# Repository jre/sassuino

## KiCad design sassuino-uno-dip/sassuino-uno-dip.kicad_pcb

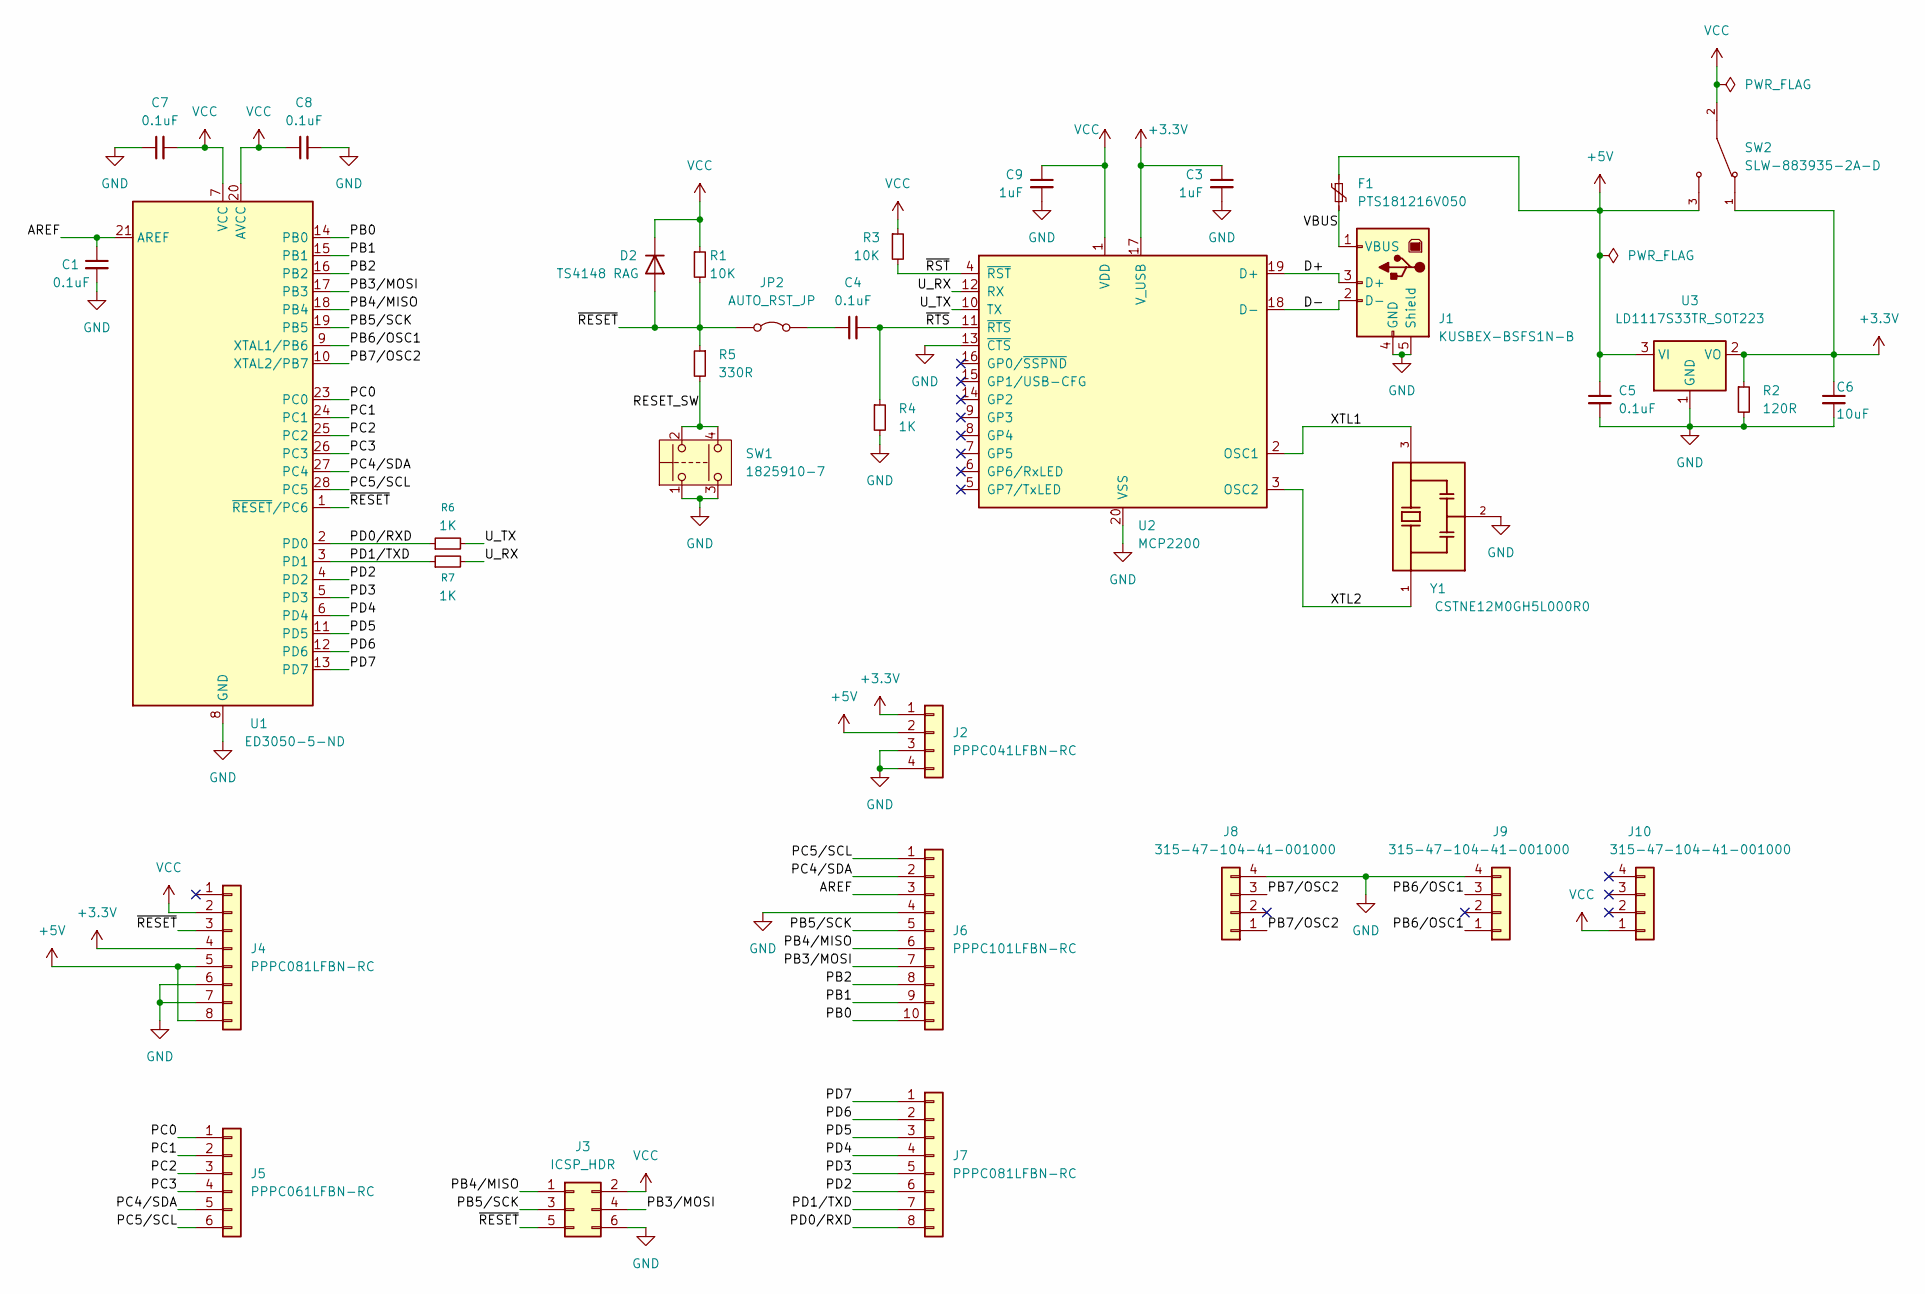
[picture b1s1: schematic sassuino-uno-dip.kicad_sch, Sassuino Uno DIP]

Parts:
C1, C4, C5, C7, C8: 0.1uF; C_1206_3216Metric
C3, C9: 1uF; C_1206_3216Metric
C6: 10uF; C_1206_3216Metric
D2: TS4148 RAG; D_1206_3216Metric
F1: PTS181216V050; Fuse_1812_4532Metric
J1: KUSBEX-BSFS1N-B; USB_B_Lumberg_2411_02_Horizontal
J2: PPPC041LFBN-RC; PinSocket_1x04_P2.54mm_Vertical
J3: ICSP_HDR; PinHeader_2x03_P2.54mm_Vertical
J4, J7: PPPC081LFBN-RC; PinSocket_1x08_P2.54mm_Vertical
J5: PPPC061LFBN-RC; PinSocket_1x06_P2.54mm_Vertical
J6: PPPC101LFBN-RC; PinSocket_1x10_P2.54mm_Vertical
J8, J9, J10: 315-47-104-41-001000; PinSocket_1x04_P2.54mm_Vertical_LowProfile
JP2: AUTO_RST_JP; PinHeader_1x02_P2.54mm_Vertical
R1, R3: 10K; R_1206_3216Metric
R2: 120R; R_1206_3216Metric
R4, R6, R7: 1K; R_1206_3216Metric
R5: 330R; R_1206_3216Metric
SW1: 1825910-7; SW4_1825910-B_TEC
SW2: SLW-883935-2A-D; SW_SLW-883935-2A-D; PARTREV 1.01
U1: ED3050-5-ND; DIP-28_W7.62mm_Socket_LongPads
U2: MCP2200; SOIC-20W_7.5x12.8mm_P1.27mm
U3: LD1117S33TR_SOT223; SOT-223-3_TabPin2
Y1: CSTNE12M0GH5L000R0; OSC_CSTNE12M0GH5L000R0; PARTREV JGC42-8858A

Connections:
+3.3V: C3.1, C6.1, J2.1, J4.4, R2.1, SW2.1, U2.17 (V_USB), U3.2 (VO)
+5V: C5.1, F1.1, J2.2, J4.5, J4.8, SW2.3, U3.3 (VI)
/AREF: C1.1, J6.3, U1.21 (AREF)
/D+: J1.3 (D+), U2.19 (D+)
/D-: J1.2 (D-), U2.18 (D-)
/PB0: J6.10, U1.14 (PB0)
/PB1: J6.9, U1.15 (PB1)
/PB2: J6.8, U1.16 (PB2)
/PB3/MOSI: J3.4, J6.7, U1.17 (PB3)
/PB4/MISO: J3.1, J6.6, U1.18 (PB4)
/PB5/SCK: J3.3, J6.5, U1.19 (PB5)
/PB6/OSC1: J9.1, J9.3, U1.9 (XTAL1/PB6)
/PB7/OSC2: J8.1, J8.3, U1.10 (XTAL2/PB7)
/PC0: J5.1, U1.23 (PC0)
/PC1: J5.2, U1.24 (PC1)
/PC2: J5.3, U1.25 (PC2)
/PC3: J5.4, U1.26 (PC3)
/PC4/SDA: J5.5, J6.2, U1.27 (PC4)
/PC5/SCL: J5.6, J6.1, U1.28 (PC5)
/PD0/RXD: J7.8, R6.1, U1.2 (PD0)
/PD1/TXD: J7.7, R7.1, U1.3 (PD1)
/PD2: J7.6, U1.4 (PD2)
/PD3: J7.5, U1.5 (PD3)
/PD4: J7.4, U1.6 (PD4)
/PD5: J7.3, U1.11 (PD5)
/PD6: J7.2, U1.12 (PD6)
/PD7: J7.1, U1.13 (PD7)
/RESET_SW: R5.2, SW1.2, SW1.4
/U_RX: R7.2, U2.12 (RX)
/U_TX: R6.2, U2.10 (TX)
/VBUS: F1.2, J1.1 (VBUS)
/XTL1: U2.2 (OSC1), Y1.3
/XTL2: U2.3 (OSC2), Y1.1
/~RESET: D2.2 (A), J3.5, J4.3, JP2.1 (A), R1.2, R5.1, U1.1 (~RESET/PC6)
/~RST: R3.2, U2.4 (~RST)
/~RTS: C4.2, R4.1, U2.11 (~RTS)
GND: C1.2, C3.2, C5.2, C6.2, C7.1, C8.2, C9.2, J1.4 (GND), J1.5 (Shield), J2.3, J2.4, J3.6, J4.6, J4.7, J6.4, J8.4, J9.4, R2.2, R4.2, SW1.1, SW1.3, U1.8 (GND), U1.22 (GND), U2.13 (~CTS), U2.20 (VSS), U3.1 (GND), Y1.2
unnamed: C4.1, JP2.2 (B)
VCC: C7.2, C8.1, C9.1, D2.1 (K), J3.2, J4.2, J10.1, R1.1, R3.1, SW2.2, U1.7 (VCC), U1.20 (AVCC), U2.1 (VDD)

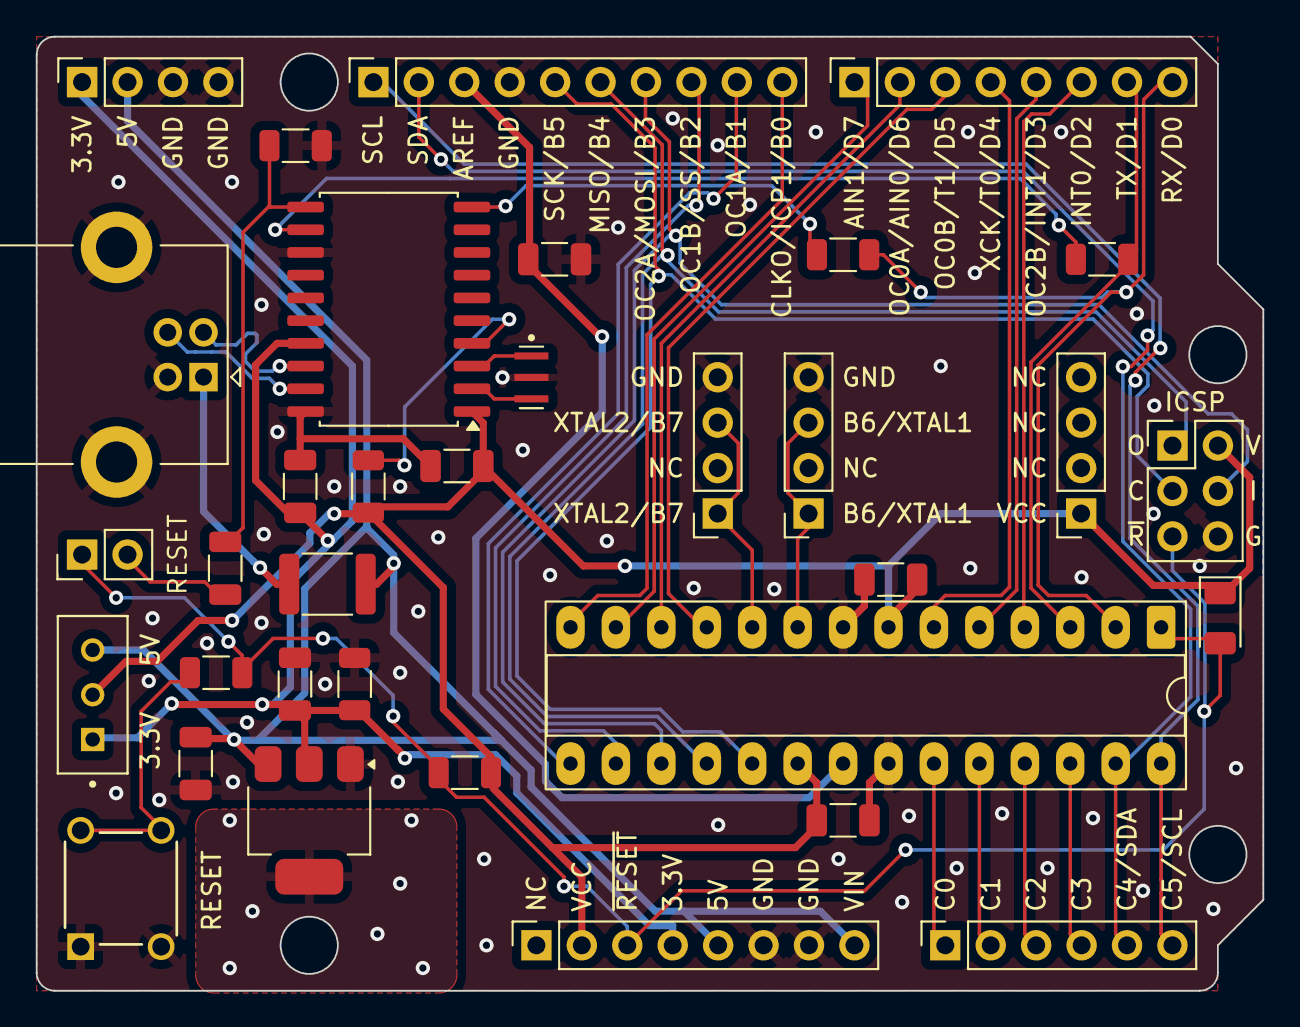
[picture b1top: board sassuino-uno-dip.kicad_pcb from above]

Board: 2 copper layers, 68.6 x 53.3 mm, 34 parts (0 on the bottom side), 39 nets.

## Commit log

2025-06-02 Import Sassuino Uno DIP project
2025-06-02 Ignore the kicad backup files.
2025-06-02 Move symbol/footprint/3d libraries under lib directory
2025-06-02 Add the actual footprint/model of the pushbutton switch I'm using.
2025-06-02 Add a clamp diode to the reset circuit.
2025-06-02 Rotate oscillator 3d model correctly.
2025-06-02 Add missing PWR_FLAG so the schematic passes the ERC again.
2025-06-03 Move decoupling capacitors closer to the IC pins.
    Also connect the caps' ground pad directly to the IC ground pin,
    rather than to the ground plane.
2025-06-03 Move RESET# protection diode next to the MCU input pin.
2025-06-03 Connect the Vin header pin.
2025-06-03 Improve the reset circuit.
    Add a 330R between the pushbutton reset switch and the capacitor, as
    per the AVR hardware design doc.
    Pull down the RTS# side of the capacitor with a 1K like in the Arduino
    schematic.
2025-06-03 Remove a generated file that was committed by mistake.
2025-06-03 Ignore generated BOM files
2025-06-05 Update to kicad 9
    Various minor tweaks to PCB traces to satisfy the DRC.
    Use a generic 3d model for the slide switch.
2025-06-05 Minor tweaks to PCB traces and copper fill zones.
2025-06-06 Equalize length of differential usb traces.
2025-06-06 Add a polyfuse on VBUS.
    Also ditch the VBUS decoupling cap, I don't recall why I added it.
2025-06-06 Remove the diode between the two LDOs, I don't remember why it was there.
2025-06-07 Replace crystal header 3d model with the part I'll likely be using.
2025-06-07 Various cosmetic tweaks.
    Switch a few 3d models to the part I'm using.
    Update the value of a few symbols to the part number.
    Tweak a few traces and silkscreen bits.
2025-06-07 Clean up power traces a bit.
2025-06-07 Move the auto-reset enable header out of the way of shields.
2025-06-07 Add fill out part numbers in schematic
2025-06-08 Add a couple resistors to protect the MCP2200's TX/RX pins from the MCU.
2025-06-09 Bump dates and configure fabrication output directory.
2025-06-15 Adjust position of oscillator headers and nearby cap.
    This is to allow a crystal with 200 mil leads to be soldered, while
    leaving the headers unpopulated.
    There might not quite be enough room to solder a 14-dip oscillator in
    place of the other two headers, but I don't think I would find that
    useful.
    Also tweak a few vias to avoid intersecting with the silkscreen.
